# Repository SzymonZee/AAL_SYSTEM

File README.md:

# AAL_SYSTEM
Project of  the Ambient  Asistant living system

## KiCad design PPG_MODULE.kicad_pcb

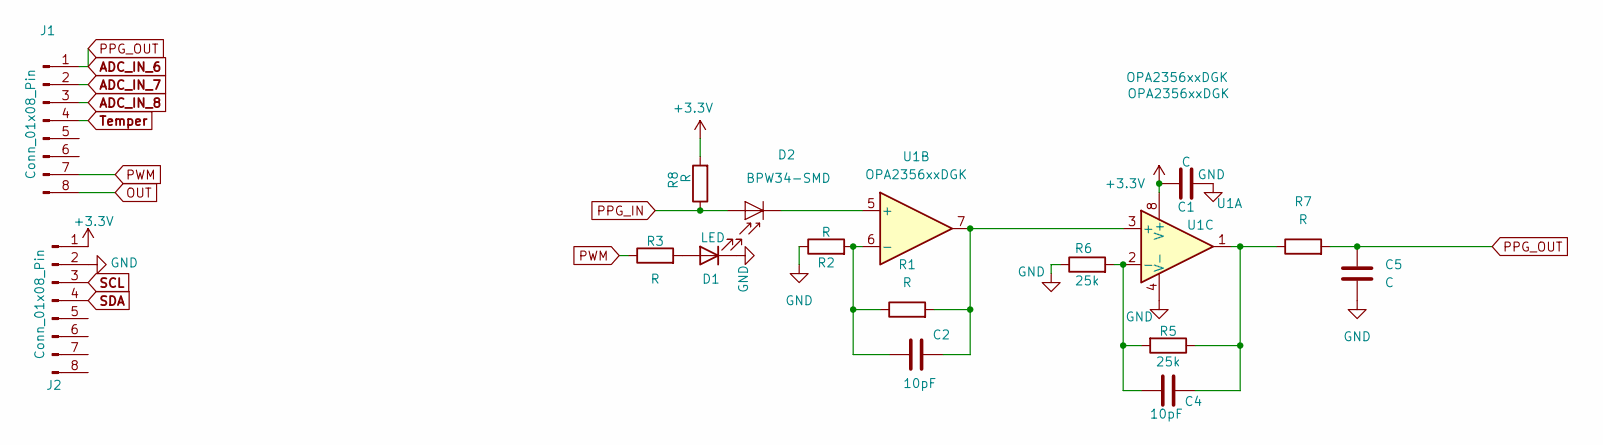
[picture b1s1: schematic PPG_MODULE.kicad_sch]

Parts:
C1, C5: C; C_0603_1608Metric_Pad1.08x0.95mm_HandSolder
C2, C4: 10pF; C_0603_1608Metric_Pad1.08x0.95mm_HandSolder
D1: LED; SFH4250S_2P9X3P4_OSR
D2: BPW34-SMD; Osram_BPW34S-SMD
J1, J2: Conn_01x08_Pin; PinSocket_1x08_P2.00mm_Vertical
R1: R
R2, R3, R7, R8: R; R_0603_1608Metric_Pad0.98x0.95mm_HandSolder
R5, R6: 25k; R_0603_1608Metric_Pad0.98x0.95mm_HandSolder
U1: OPA2356xxDGK; D8

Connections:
+3.3V: C1.1, J2.1, R8.2, U1.8 (V+)
ADC_IN_6: C5.2, J1.1, R7.2
ADC_IN_7: J1.2
ADC_IN_8: J1.3
GND: C1.2, C5.1, D1.1 (K), J2.2, R2.1, R6.1, U1.4 (V-)
unnamed: C4.1, R5.1, R7.1, U1.1
unnamed: D1.2 (A), R3.2
unnamed: D2.1 (K), U1.5 (+)
unnamed: C2.1, R1.2, U1.3 (+), U1.7
unnamed: C4.2, R5.2, R6.2, U1.2 (-)
unnamed: C2.2, R1.1, R2.2, U1.6 (-)
OUT: J1.8
PPG_IN: D2.2 (A), R8.1
PWM: J1.7, R3.1
SCL: J2.3
SDA: J2.4
Temper: J1.4

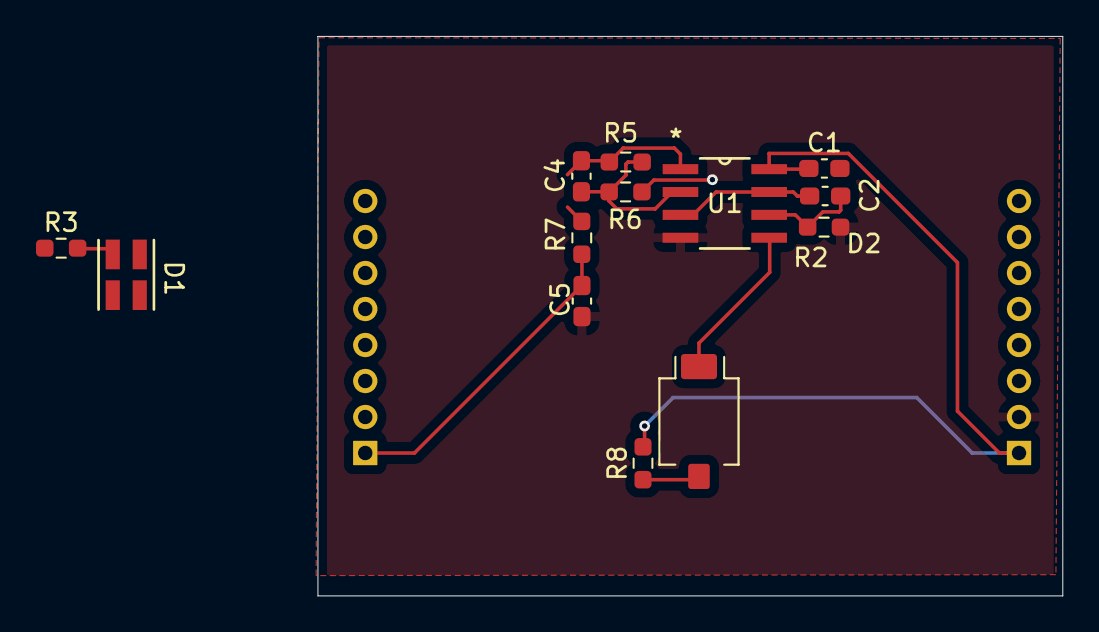
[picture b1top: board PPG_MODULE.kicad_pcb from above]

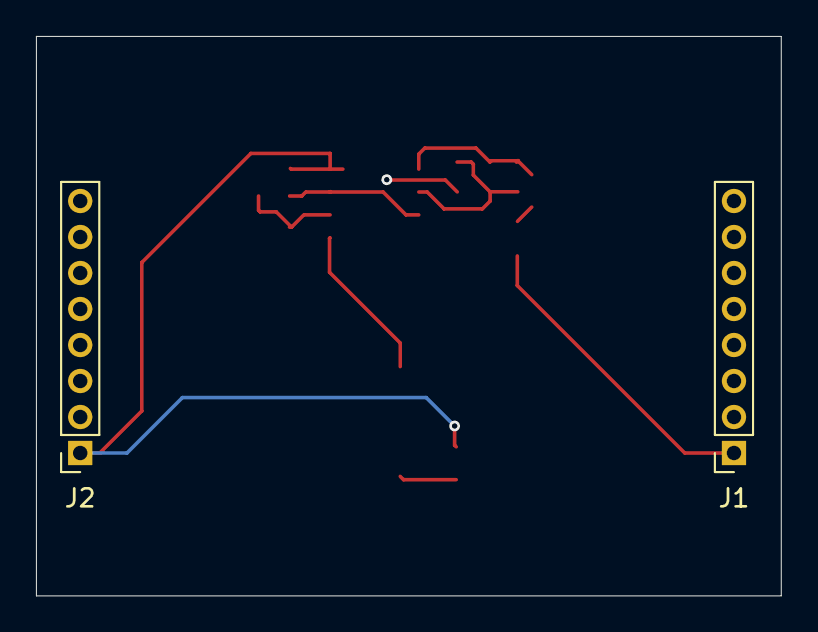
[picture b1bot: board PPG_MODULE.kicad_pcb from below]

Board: 2 copper layers, 41.4 x 31.1 mm, 15 parts (2 on the bottom side), 11 nets.

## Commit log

2024-11-09 PPG Module for AAL System
2025-08-11 Add or update the Azure App Service build and deployment workflow config
